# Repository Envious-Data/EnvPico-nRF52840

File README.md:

# EnvOpenPico
A nRF52840 MCU board that is in the size of a raspberry pi pico.

### Info
like the other boards Ive designed, I wanted to make sure this would fit in place of a raspberry pi pico incase you wanted wifi + bluetooth and battery on one board instead of a stack of packs for the pi pico.

this is intended to be used with my keyboards again like the other boards but ive made sure to include a decently powerful PMIC just so its capable of other things too, the BQ24072RGT should be capable of upto 1.5A output but around 500mA charging.

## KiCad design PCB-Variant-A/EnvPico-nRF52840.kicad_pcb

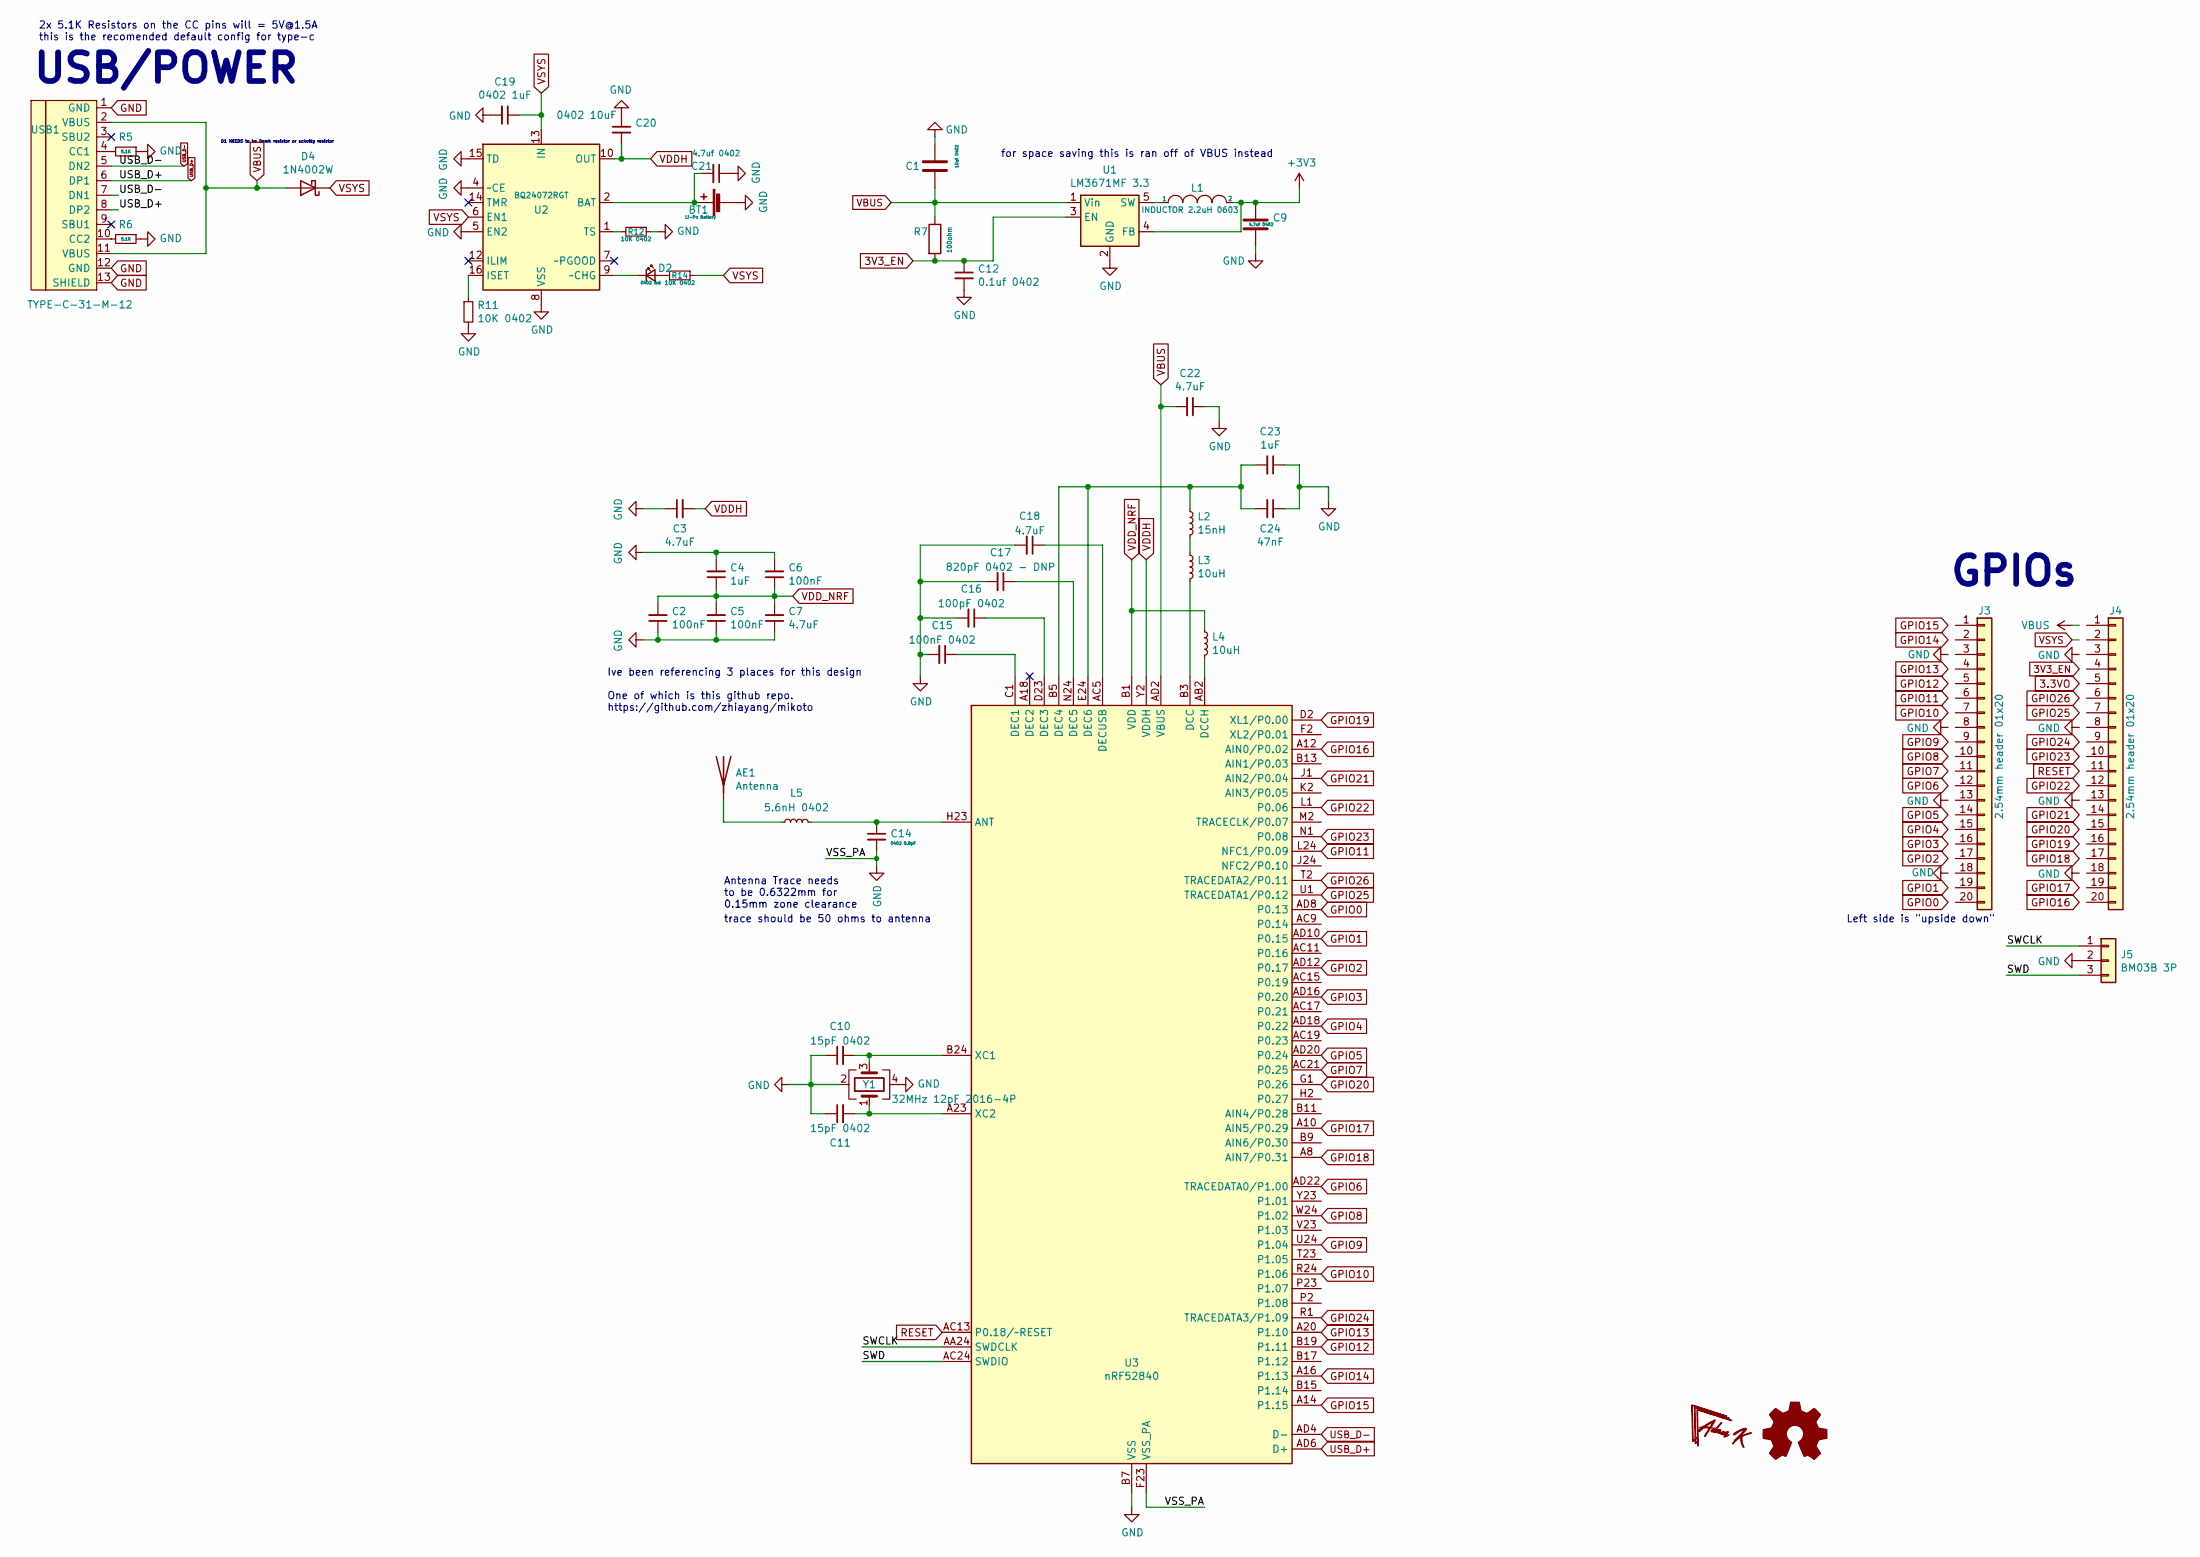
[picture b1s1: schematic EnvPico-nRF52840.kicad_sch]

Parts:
AE1: Antenna; Johanson_2450AT43F0100
BT1: Li-Po Battery; JST_PH_B2B-PH-K_1x02_P2.00mm_Vertical
C1: 10uf 0402; C_0402_1005Metric
C2, C5, C6: 100nF; C_0402_1005Metric; Manufacturer Part CL05B104KA5NNNC; LCSC Part C1525
C3, C7, C18, C22: 4.7uF; C_0402_1005Metric; Manufacturer Part CL05A475KP5NRNC; LCSC Part C368809
C4, C23: 1uF; C_0402_1005Metric; Manufacturer Part CL05A105KO5NNNC; LCSC Part C52923
C9, C21: 4.7uf 0402; C_0402_1005Metric
C10, C11: 15pF 0402; C_0402_1005Metric
C12: 0.1uf 0402; C_0402_1005Metric
C14: 0402 0.8pF; C_0402_1005Metric
C15: 100nF 0402; C_0402_1005Metric; Manufacturer Part CL05B104KA5NNNC; LCSC Part C1525
C16: 100pF 0402; C_0402_1005Metric; Manufacturer Part CL05C101JB5NNNC; LCSC Part C26409
C17: 820pF 0402 - DNP; C_0402_1005Metric; Manufacturer Part CL05B102KB5NNNC; LCSC Part C14442
C19: 0402 1uF; C_0402_1005Metric
C20: 0402 10uF; R_0402_1005Metric
C24: 47nF; C_0402_1005Metric; Manufacturer Part CL05B473KO5NNNC; LCSC Part C307434
D2: 0402 led; LED_0402_1005Metric
D4: 1N4002W; D_SOD-123
J3, J4: 2.54mm header 01x20; PinHeader_1x20_P2.54mm_Vertical_castelated
J5: BM03B 3P; JST_SUR_BM03B-SURS-TF_1x03-1MP_P0.80mm_Vertical
L1: INDUCTOR 2.2uH 0603; L_0603_1608Metric
L2: 15nH; C_0402_1005Metric; Manufacturer Part MLG1005S15NJT000; LCSC Part C76763
L3, L4: 10uH; L_0603_1608Metric; Manufacturer Part MLF1608E100KTD00; LCSC Part C76732
L5: 5.6nH 0402; L_0402_1005Metric
R5, R6: 5.1K; R_0402_1005Metric
R7: 100ohm; R_0402_1005Metric
R11, R12, R14: 10K 0402; R_0402_1005Metric
U1: LM3671MF 3.3; TSOT-23-5
U2: BQ24072RGT; VQFN-16-1EP_3x3mm_P0.5mm_EP1.6x1.6mm
U3: nRF52840; Nordic_AQFN-73-1EP_7x7mm_P0.5mm
USB1: TYPE-C-31-M-12; HRO-TYPE-C-31-M-12
Y1: 32MHz 12pF 2016-4P; Crystal_SMD_2016-4Pin_2.0x1.6mm

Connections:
3V3_EN: C12.1, R7.2, U1.3 (EN)
+3V3: C9.1, L1.2, U1.4 (FB)
/SWCLK: J5.1, U3.AA24 (SWDCLK)
/SWD: J5.3, U3.AC24 (SWDIO)
GND: BT1.2 (-), C1.2, C2.1, C3.1, C4.2, C5.1, C6.2, C7.1, C9.2, C10.1, C11.1, C12.2, C14.2, C15.2, C16.2, C17.2, C18.2, C19.2, C20.1, C21.1, C22.1, C23.1, C24.1, J5.2, R5.1, R6.1, R11.2, R12.1, U1.2 (GND), U2.4 (~CE), U2.5 (EN2), U2.8 (VSS), U2.15 (TD), U2.17 (VSS), U3.B7 (VSS), U3.EP (VSS), U3.F23 (VSS_PA), USB1.1 (GND), USB1.12 (GND), USB1.13 (SHIELD), Y1.2, Y1.4
GPIO0: U3.AD8 (P0.13)
GPIO1: U3.AD10 (P0.15)
GPIO2: U3.AD12 (P0.17)
GPIO3: U3.AD16 (P0.20)
GPIO4: U3.AD18 (P0.22)
GPIO5: U3.AD20 (P0.24)
GPIO6: U3.AD22 (TRACEDATA0/P1.00)
GPIO7: U3.AC21 (P0.25)
GPIO8: U3.W24 (P1.02)
GPIO9: U3.U24 (P1.04)
GPIO10: U3.R24 (P1.06)
GPIO11: U3.L24 (NFC1/P0.09)
GPIO12: U3.B19 (P1.11)
GPIO13: U3.A20 (P1.10)
GPIO14: U3.A16 (P1.13)
GPIO15: U3.A14 (P1.15)
GPIO16: U3.A12 (AIN0/P0.02)
GPIO17: U3.A10 (AIN5/P0.29)
GPIO18: U3.A8 (AIN7/P0.31)
GPIO19: U3.D2 (XL1/P0.00)
GPIO20: U3.G1 (P0.26)
GPIO21: U3.J1 (AIN2/P0.04)
GPIO22: U3.L1 (P0.06)
GPIO23: U3.N1 (P0.08)
GPIO24: U3.R1 (TRACEDATA3/P1.09)
GPIO25: U3.U1 (TRACEDATA1/P0.12)
GPIO26: U3.T2 (TRACEDATA2/P0.11)
unnamed: AE1.1 (A), L5.1
unnamed: BT1.1 (+), C21.2, U2.2 (BAT), U2.3 (BAT)
unnamed: D2.2 (A), R14.2
unnamed: D2.1 (K), U2.9 (~CHG)
unnamed: L2.2, L3.1
unnamed: L1.1, U1.5 (SW)
unnamed: R11.1, U2.16 (ISET)
unnamed: R12.2, U2.1 (TS)
unnamed: C14.1, L5.2, U3.H23 (ANT)
unnamed: L3.2, U3.B3 (DCC)
unnamed: L4.2, U3.AB2 (DCCH)
unnamed: C15.1, U3.C1 (DEC1)
unnamed: C16.1, U3.D23 (DEC3)
unnamed: C23.2, C24.2, L2.1, U3.B5 (DEC4), U3.E24 (DEC6)
unnamed: C17.1, U3.N24 (DEC5)
unnamed: C18.1, U3.AC5 (DECUSB)
unnamed: C10.2, U3.B24 (XC1), Y1.3
unnamed: C11.2, U3.A23 (XC2), Y1.1
unnamed: R5.2, USB1.4 (CC1)
unnamed: R6.2, USB1.10 (CC2)
RESET: U3.AC13 (P0.18/~RESET)
USB_D+: U3.AD6 (D+), USB1.6 (DP1), USB1.8 (DP2)
USB_D-: U3.AD4 (D-), USB1.5 (DN2), USB1.7 (DN1)
VBUS: C1.1, C22.2, D4.2 (A), R7.1, U1.1 (Vin), U3.AD2 (VBUS), USB1.2 (VBUS), USB1.11 (VBUS)
VDDH: C3.2, C20.2, U2.10 (OUT), U2.11 (OUT), U3.Y2 (VDDH)
VDD_NRF: C2.2, C4.1, C5.2, C6.1, C7.2, L4.1, U3.A22 (VDD), U3.AD14 (VDD), U3.AD23 (VDD), U3.B1 (VDD), U3.W1 (VDD)
VSYS: C19.1, D4.1 (K), R14.1, U2.6 (EN1), U2.13 (IN)

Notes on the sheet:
Ive been referencing 3 places for this design One of which is this github repo. https://github.com/zhiayang/mikoto
D1 NEEDS to be 0omh resistor or schotky resistor
2x 5.1K Resistors on the CC pins will = 5V@1.5A this is the recomended default config for type-c
Antenna Trace needs to be 0.6322mm for 0.15mm zone clearance
USB/POWER
GPIOs
trace should be 50 ohms to antenna
for space saving this is ran off of VBUS instead
Left side is "upside down"

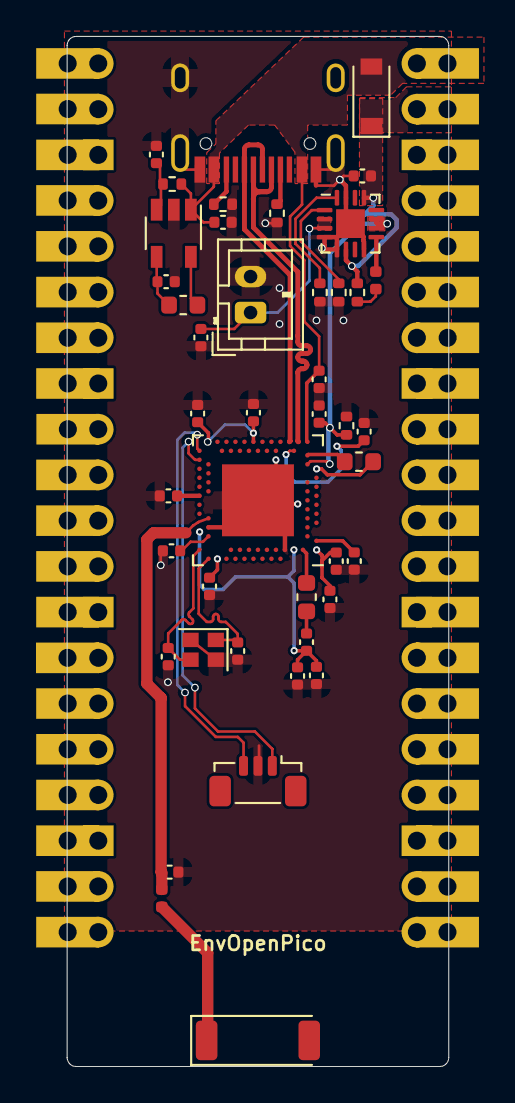
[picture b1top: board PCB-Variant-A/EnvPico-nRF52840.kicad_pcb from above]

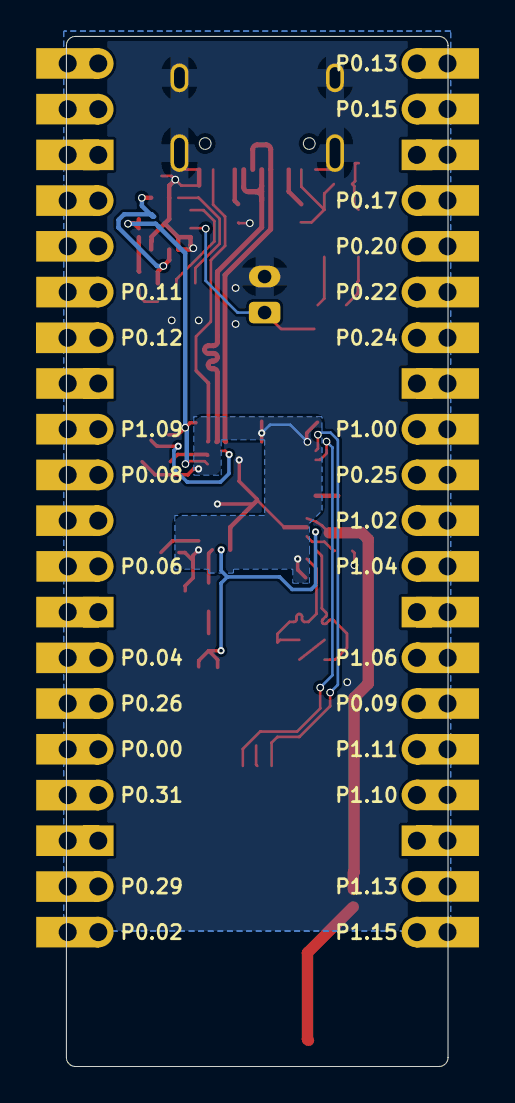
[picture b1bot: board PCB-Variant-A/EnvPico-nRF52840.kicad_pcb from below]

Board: 2 copper layers, 21.2 x 57.2 mm, 45 parts (2 on the bottom side), 31 nets.

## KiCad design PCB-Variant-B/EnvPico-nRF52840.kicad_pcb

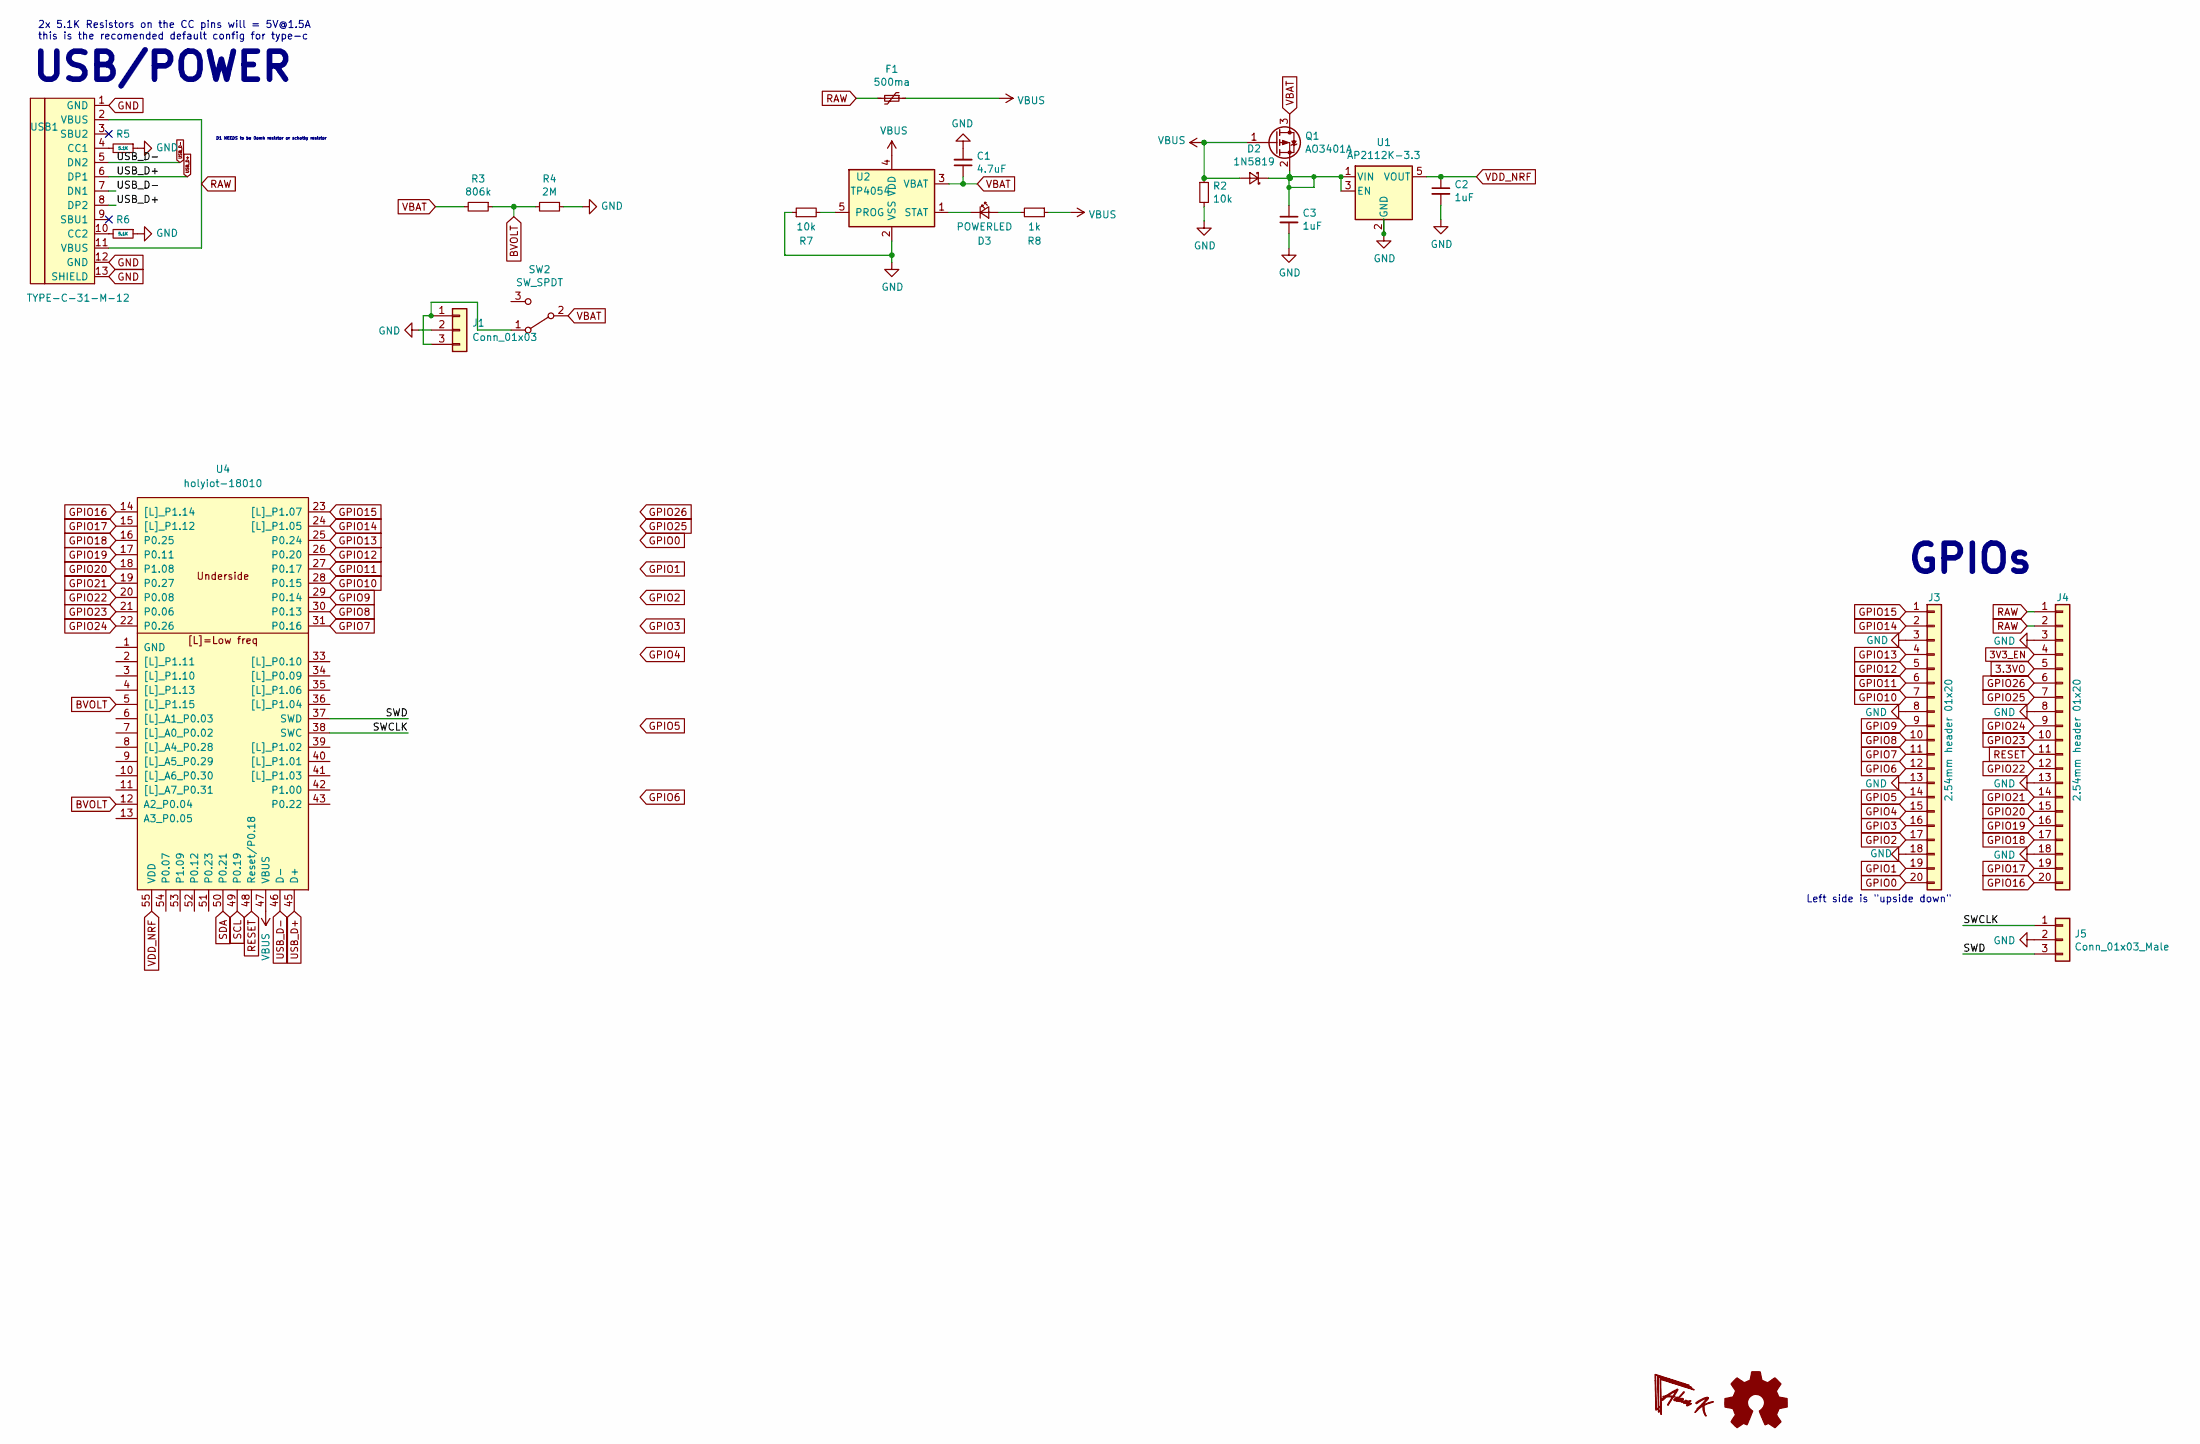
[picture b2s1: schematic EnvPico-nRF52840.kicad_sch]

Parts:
C1: 4.7uF; C_0402_1005Metric
C2, C3: 1uF; C_0402_1005Metric
D2: 1N5819; D_SOD-123
D3: POWERLED; D_0402_1005Metric
F1: 500ma; Fuse_0805_2012Metric
J1: Conn_01x03; JST_SH_BM03B-SRSS-TB_1x03-1MP_P1.00mm_Vertical
J3, J4: 2.54mm header 01x20; PinHeader_1x20_P2.54mm_Vertical_castelated
J5: Conn_01x03_Male; PinHeader_1x03_P2.54mm_Vertical
Q1: AO3401A; SOT-23
R2, R7: 10k; R_0402_1005Metric
R3: 806k; R_0402_1005Metric
R4: 2M; R_0402_1005Metric
R5, R6: 5.1K; R_0402_1005Metric
R8: 1k; R_0402_1005Metric
SW2: SW_SPDT; PinHeader_1x03_P1.00mm_Vertical
U1: AP2112K-3.3; SOT-23-5
U2: TP4054; SOT-23-5
U4: holyiot-18010
USB1: TYPE-C-31-M-12; HRO-TYPE-C-31-M-12

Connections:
3.3VO: J4.5
3V3_EN: J4.4
/SWCLK: J5.1, U4.38 (SWC)
/SWD: J5.3, U4.37 (SWD)
BVOLT: R3.1, R4.2, U4.5 ([L]_P1.15), U4.12 (A2_P0.04)
GPIO0: J3.20
GPIO1: J3.19
GPIO2: J3.17
GPIO3: J3.16
GPIO4: J3.15
GPIO5: J3.14
GPIO6: J3.12
GPIO7: J3.11, U4.31 (P0.16)
GPIO8: J3.10, U4.30 (P0.13)
GPIO9: J3.9, U4.29 (P0.14)
GPIO10: J3.7, U4.28 (P0.15)
GPIO11: J3.6, U4.27 (P0.17)
GPIO12: J3.5, U4.26 (P0.20)
GPIO13: J3.4, U4.25 (P0.24)
GPIO14: J3.2, U4.24 ([L]_P1.05)
GPIO15: J3.1, U4.23 ([L]_P1.07)
GPIO16: J4.20, U4.14 ([L]_P1.14)
GPIO17: J4.19, U4.15 ([L]_P1.12)
GPIO18: J4.17, U4.16 (P0.25)
GPIO19: J4.16, U4.17 (P0.11)
GPIO20: J4.15, U4.18 (P1.08)
GPIO21: J4.14, U4.19 (P0.27)
GPIO22: J4.12, U4.20 (P0.08)
GPIO23: J4.10, U4.21 (P0.06)
GPIO24: J4.9, U4.22 (P0.26)
GPIO25: J4.7
GPIO26: J4.6
unnamed: C3.1, D2.1 (K), Q1.2 (S), U1.1 (VIN), U1.3 (EN)
unnamed: D3.1 (K), U2.1 (STAT)
unnamed: D3.2 (A), R8.2
unnamed: J1.1, J1.3, SW2.1 (A)
unnamed: R5.2, USB1.4 (CC1)
unnamed: R6.2, USB1.10 (CC2)
unnamed: R7.2, U2.5 (PROG)
RAW: F1.2, J4.1, J4.2, USB1.2 (VBUS), USB1.11 (VBUS)
RESET: J4.11, U4.48 (Reset/P0.18)
SCL: U4.49 (P0.19)
SDA: U4.50 (P0.21)
USB_D+: U4.45 (D+), USB1.6 (DP1), USB1.8 (DP2)
USB_D-: U4.46 (D-), USB1.5 (DN2), USB1.7 (DN1)
VBAT: C1.1, Q1.3 (D), R3.2, SW2.2 (B), U2.3 (VBAT)
VBUS: D2.2 (A), F1.1, Q1.1 (G), R2.1, R8.1, U2.4 (VDD), U4.47 (VBUS)
VDD_NRF: C2.1, U1.5 (VOUT), U4.55 (VDD)

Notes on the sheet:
D1 NEEDS to be 0omh resistor or schotky resistor
2x 5.1K Resistors on the CC pins will = 5V@1.5A this is the recomended default config for type-c
USB/POWER
GPIOs
Left side is "upside down"

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
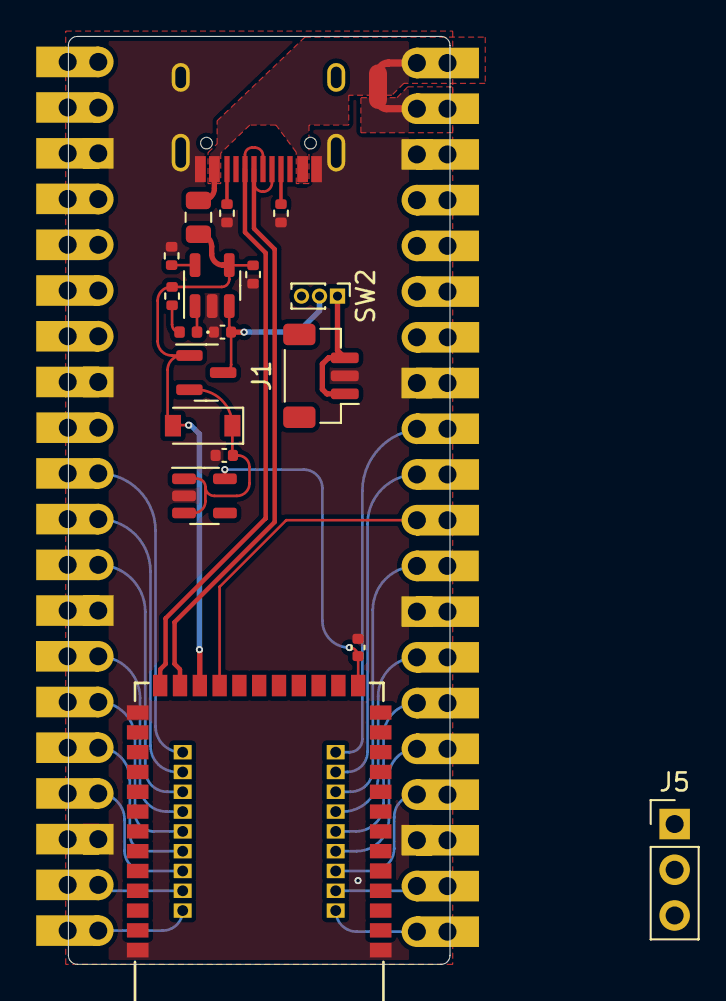
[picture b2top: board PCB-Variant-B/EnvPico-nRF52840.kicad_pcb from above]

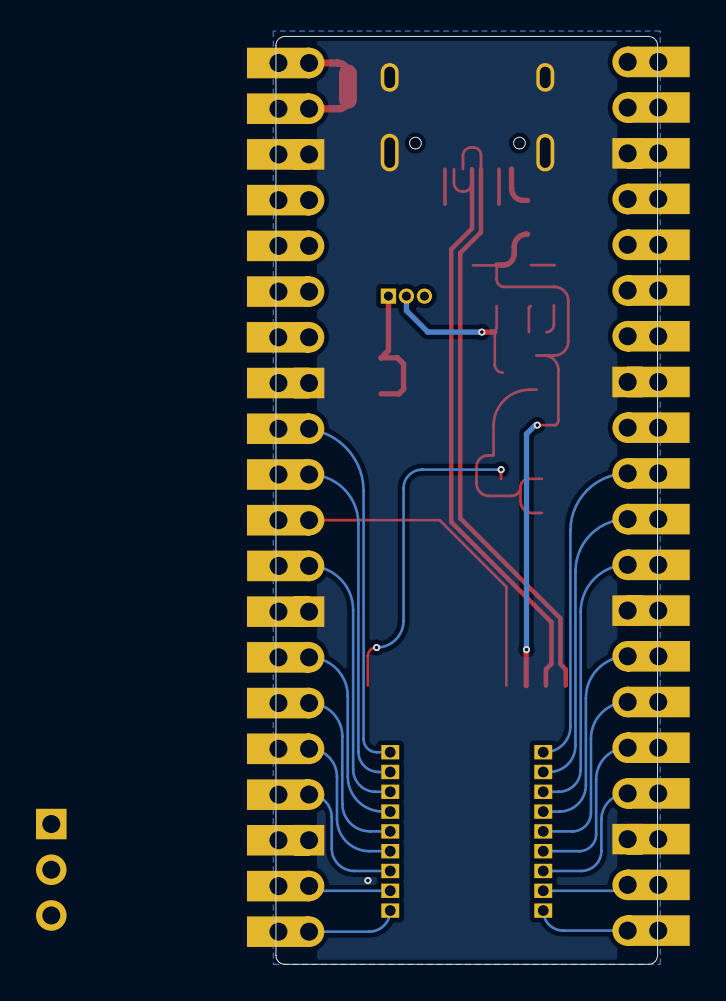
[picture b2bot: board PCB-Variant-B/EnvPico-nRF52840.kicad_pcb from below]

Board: 2 copper layers, 21.2 x 51.6 mm, 21 parts (2 on the bottom side), 36 nets.

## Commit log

2021-08-14 Initial Commit +1
2021-08-14 started adding some pins for GPIO
2021-08-14 made sure all vias are correctly placed and sized.
2021-08-17 connected all 26 GPIOs among other things.
2021-08-23 changed 2012 crystal for a 3225 size due to part availability. + went through and did a general clean up and correction per DRC.
2021-08-23 generated upto date gerber, going to start putting money aside to order this PCB.
2021-09-04 fixed a kicad derp
2021-09-04 adjusted footprint of nRF52840 a bit, adjusted few traces and via locations.
2021-09-04 moved some traces about to make sure there is good ground coverage
2021-09-05 fixed leftover silkscreen C12, couple of plane tweaks and added center marker / board dimensions on back of PCB, fixed incorrect diode footprint and in schematic
2021-09-16 some edits and corrections
2021-09-16 added silkscreen pin labels to the bottom of the PCB
2022-01-26 Corrected Antenna stuff hopefully
    this is voodoo to me so its probably still wrong.
2022-06-21 I think this is correct trace thickness for 50ohm impedance
2022-07-21 preperation to potentially make a module version
2022-10-07 made a couple of pcb variants for future use maybe
2024-05-28 added library for QFN version
2024-05-28 started re-design of board.
